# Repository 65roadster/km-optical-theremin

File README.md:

# km-optical-theremin
 Learn to SMT Class

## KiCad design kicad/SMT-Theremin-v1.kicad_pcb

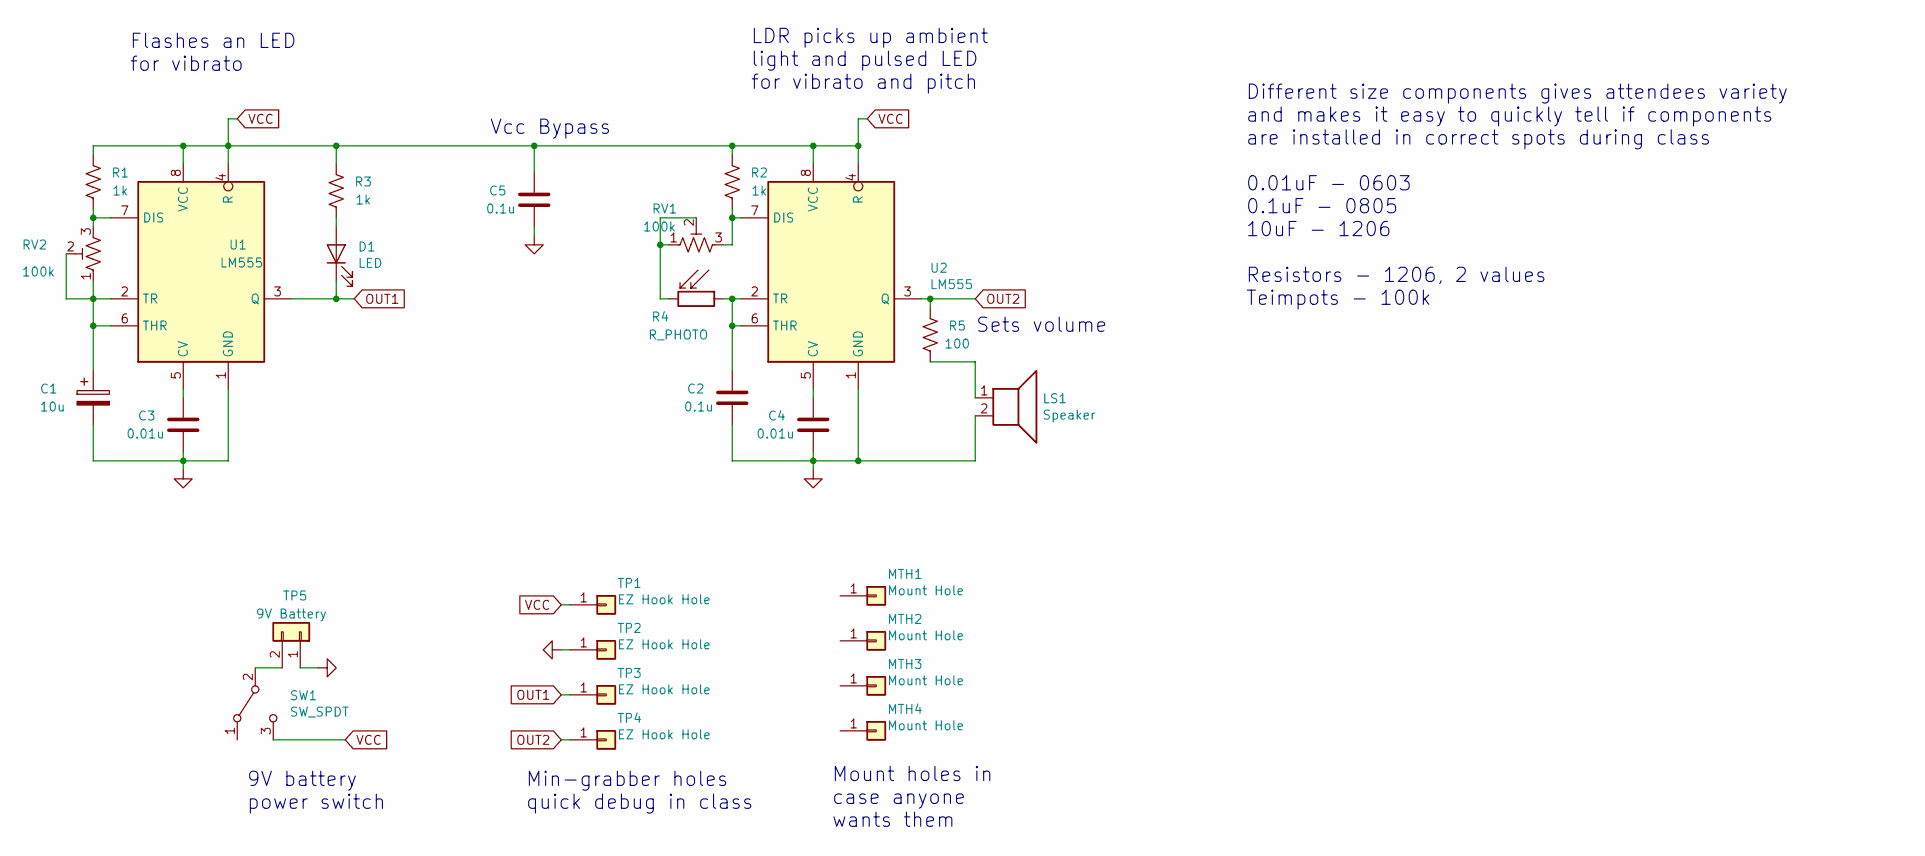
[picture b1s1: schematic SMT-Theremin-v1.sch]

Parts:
C1: 10u; C_1206_HandSoldering
C2, C5: 0.1u; C_0805_HandSoldering
C3, C4: 0.01u; C_0603_HandSoldering
D1: LED; D_0805_HandSoldering
LS1: Speaker; Speaker-40mm
MTH1, MTH2, MTH3, MTH4: Mount Hole; Mount-Hole-#4
R1, R2, R3: 1k; R_1206_HandSoldering
R4: R_PHOTO; R_LDR_5.1x4.3mm_P3.4mm_Vertical
R5: 100; R_1206_HandSoldering
RV1, RV2: 100k; Potentiometer_Vishay_TS53YJ_Vertical
SW1: SW_SPDT; KM-SPDT-Slide
TP1, TP2, TP3, TP4: EZ Hook Hole; TP-Minigrabber-Edge-Via
TP5: 9V Battery; PinHeader_1x02_P2.54mm_Vertical
U1, U2: LM555; SOIC-8_3.9x4.9mm_P1.27mm

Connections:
GND: C1.2, C2.1, C3.1, C4.1, C5.1, LS1.2, TP2.1, TP5.1, U1.1 (GND), U2.1 (GND)
unnamed: C1.1, RV2.1, RV2.2, U1.2 (TR), U1.6 (THR)
unnamed: C2.2, R4.1, U2.2 (TR), U2.6 (THR)
unnamed: C3.2, U1.5 (CV)
unnamed: C4.2, U2.5 (CV)
unnamed: D1.2 (A), R3.1
unnamed: LS1.1, R5.1
unnamed: R1.1, RV2.3, U1.7 (DIS)
unnamed: R2.1, RV1.3, U2.7 (DIS)
unnamed: R4.2, RV1.1, RV1.2
unnamed: SW1.2 (B), TP5.2
OUT1: D1.1 (K), TP3.1, U1.3 (Q)
OUT2: R5.2, TP4.1, U2.3 (Q)
VCC: C5.2, R1.2, R2.2, R3.2, SW1.3 (C), TP1.1, U1.4 (R), U1.8 (VCC), U2.4 (R), U2.8 (VCC)

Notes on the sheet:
9V battery power switch
Min-grabber holes quick debug in class
Mount holes in case anyone wants them
Flashes an LED for vibrato
LDR picks up ambient light and pulsed LED for vibrato and pitch
Different size components gives attendees variety and makes it easy to quickly tell if components are installed in correct spots during class 0.01uF - 0603 0.1uF - 0805 10uF - 1206 Resistors - 1206, 2 values Teimpots - 100k
Vcc Bypass
Sets volume

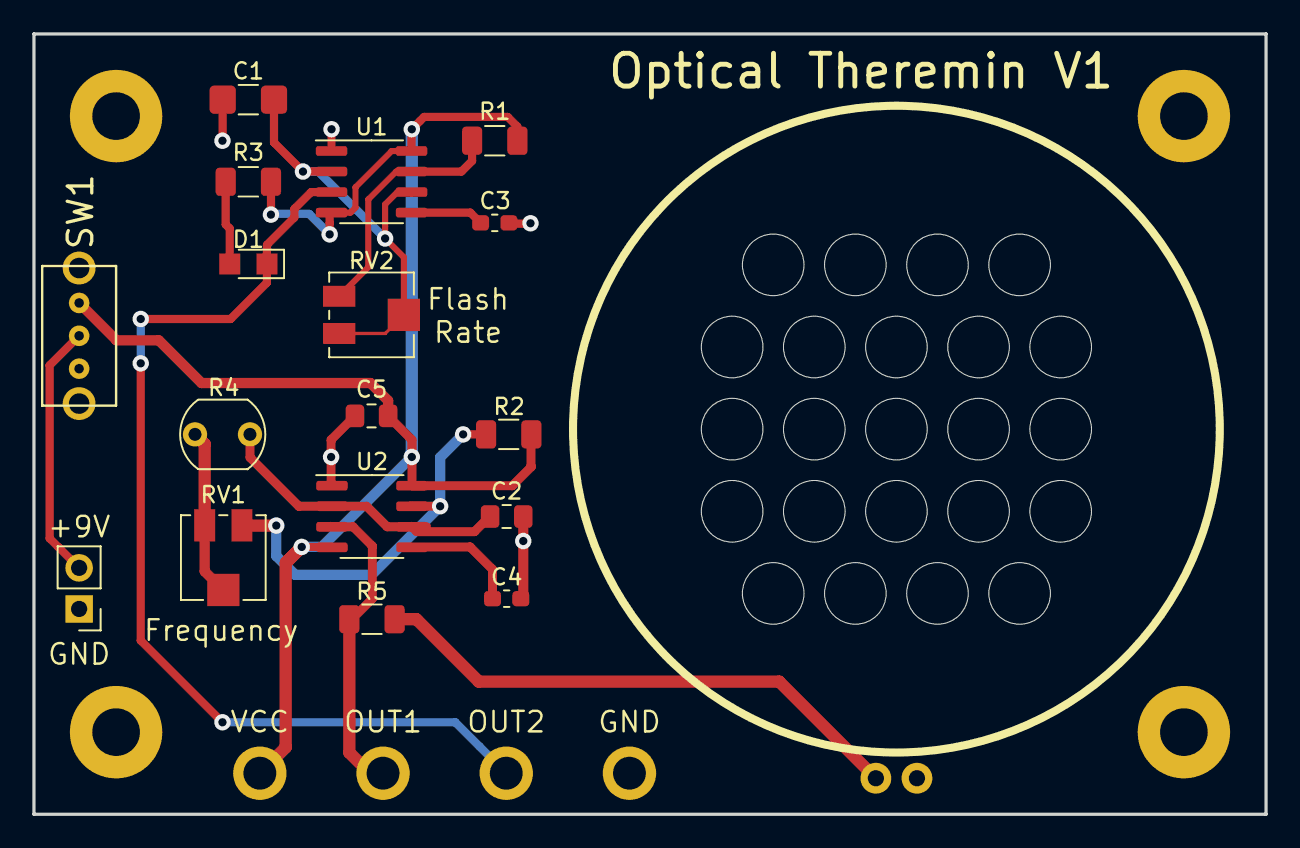
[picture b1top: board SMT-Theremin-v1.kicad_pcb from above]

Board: 2 copper layers, 76.2 x 48.3 mm, 26 parts (0 on the bottom side), 14 nets.

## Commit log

2020-06-16 FInalized schematic and layout, submit for order
2020-06-16 Layout tweaks for order
2020-11-23 instructions
